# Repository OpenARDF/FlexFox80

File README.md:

# FlexFox80
A very configurable remote-controllable 80m ARDF transmitter. It has no external buttons or switches, and contains its own webserver and is configured using most WiFi-capable devices, such as smartphones, tablets, or laptops.

Flexfox can be configured to function as an 80m "fox" transmitter for any type of Amateur Radio Direction Finding event, such as classic, sprint, or even foxoring.  

Photo: Prototype FlexFox80 Assembled with 12V 6AH Battery Underneath

<b>KiCad</b>

The KiCad folder holds files for generating the schematic, BOM, and PCB files using KiCad. 

<b>Software</b>

The Software folder holds files for compiling executable code using Atmel Studio 7. 

Photo: Prototype FlexFox80 with Transparent Cover Removed

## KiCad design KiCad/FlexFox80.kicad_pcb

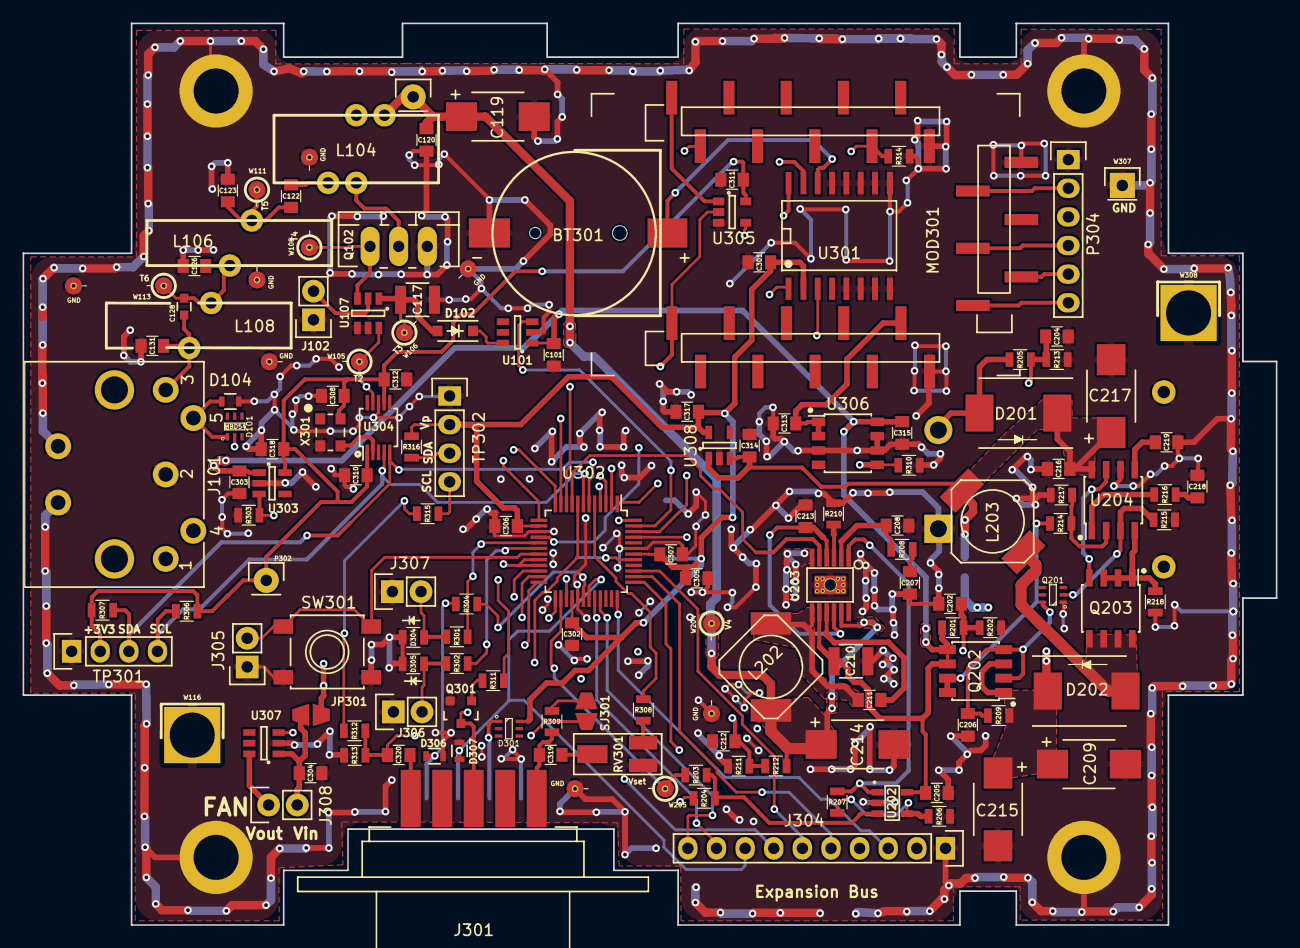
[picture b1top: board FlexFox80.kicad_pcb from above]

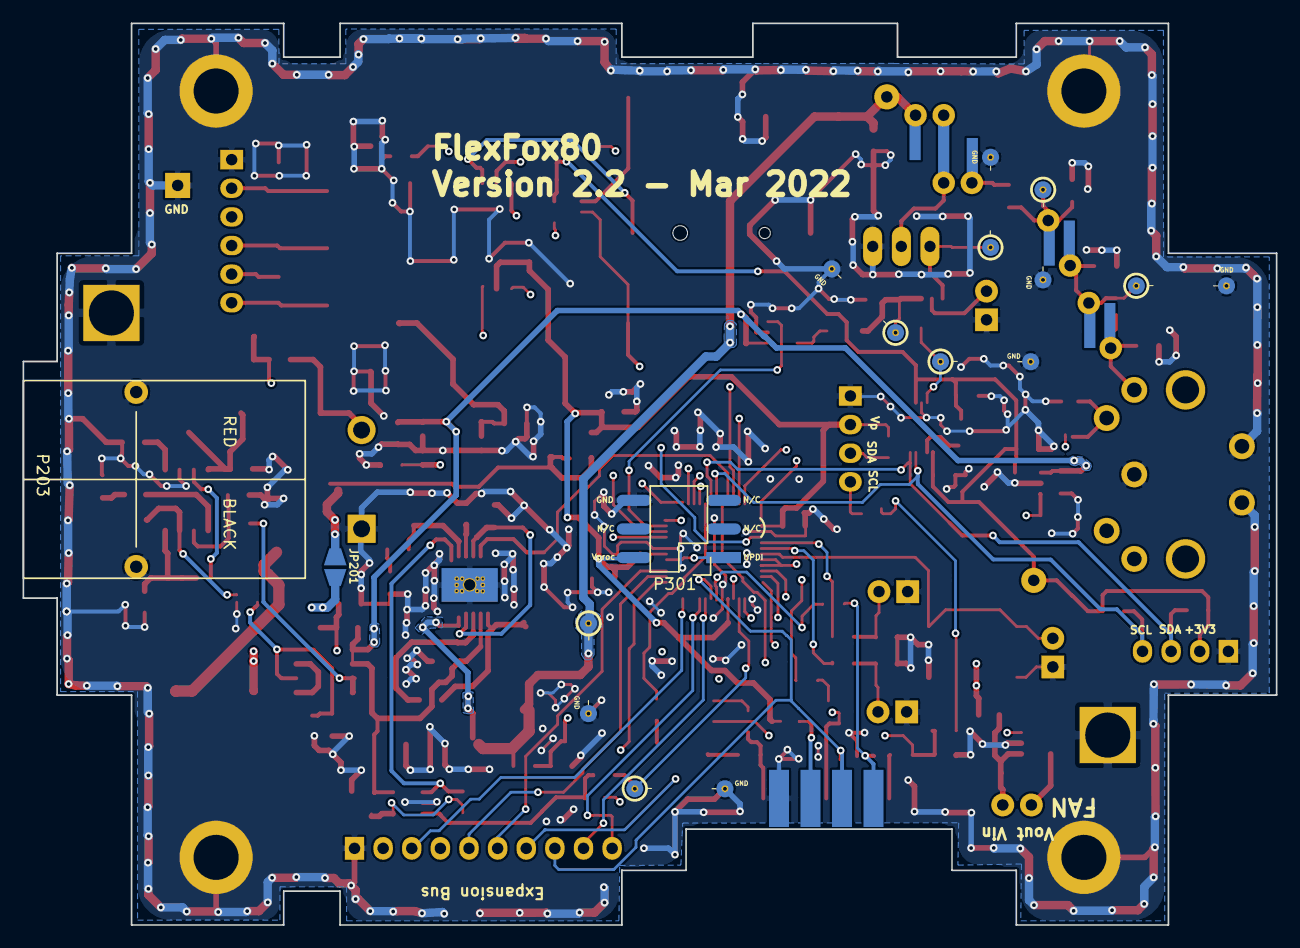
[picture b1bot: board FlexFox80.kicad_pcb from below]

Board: 4 copper layers, 111.2 x 80.0 mm, 143 parts (3 on the bottom side), 94 nets.

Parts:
BT301: CR1220; BC501SM_CR1220_BAT_Handsolder
C101, C205, C216, C304, C305: 10uF; C_0805
C117, C210: 22uF; C_1210
C119, C214, C217: 47uF low ESR; C_2917
C120, C122, C310, C312: 470nF; C_0805
C123, C131: 1100pF; C_0805
C126: 1800pF; C_0805
C128: 91pF; C_0603
C202, C204, C206, C211, C212, C302, C306, C307, C308, C311, C319, C320: 100nF; C_0805
C207: 270pF; C_0805
C208: 10pF; C_0805
C209, C215: 150uF low ESR; C_2917
C213, C219, C301: 1uF; C_0805
C218: 10nF; C_0805
C303, C313, C314, C315, C317, C318: 4.7uF; C_0805
D101, D301: MBD54; SOT-363-0.65_MBD54
D102: 4.7V; SOD-123
D104, D306, D307: ESD; R_0603
D201, D202: B530; DO-214AB
D304: GREEN; D_0805
D305: RED; D_0805
J101: DIN-5_180degree; SDF-50J
J102, J305, J306, J307, J308: Conn_01x02; Pin_Header_Straight_1x02
J203: V4; Pin_Header_Straight_1x01_circle_pad
J301: DB9_Female; DB9F_CI
J304: Conn_01x10; Pin_Header_Straight_1x10
JP201: Boost Bypass; Solder-Jumper-NO-SMD-Pad_Small
JP301: Jumper_NO_Small; Solder-Jumper-NO-SMD-Pad_Small
L104: 9T #24 Bifilar T50-43; Toroid_T-50A_TH_BF_CT_Vertical
L106, L108: 2.7uH; Toroid_T-60_2TH_Vertical
L202, L203: 6.8uH; CDR7D28MN
MOD301: HUZZAH_ESP8266_Breakout; Adafruit_HUZZAH_ESP8266_Breakout_SM
P203: Power Pole; PowerPole-ASMPP30-1x2
P301: ISP/PDI; SM_Pin_Header_Straight_2x03
P302: Thru; Pin_Header_Straight_1x01
P304: Header; Pin_Header_Straight_1x06
Q102: IRF610; TO-220_Neutral123_Vertical_LargePads
Q201: MUN5213DW1; SOT-363-0.65
Q202: DMP4025LSD; SOIC-8_3.9x4.9mm_Pitch1.27mm
Q203: RJK0354DSP; SOIC-8_3.9x4.9mm_Pitch1.27mm
Q301: PN2222A; SOT-23
R201, R205, R212: 162k; R_0805
R202: 49.9k; R_0805
R203, R206, R208: 27k; R_0805
R204: 392k; R_0805
R207, R209, R210, R308, R313: 100k; R_0805
R211, R213, R214, R215, R216, R303, R306, R307, R310, R311, R315, R316: 10k; R_0805
R217: 1.1k; R_0805
R218: 0.01 0.5W; R_0805
R301, R302: 470; R_0805
R304: 10; R_0805
R309: 2.2k; R_0805
R312, R314: 560k; R_0805
RV301: 10k Pot; Potentiometer_ST32ET_Handsolder
SJ301: SolderJumper_2_Open; Solder-Jumper-NO-SMD-Pad_Small
SW301: SPST; PTS645SL50SMTR92
TP301: I2C1; Pin_Header_Straight_1x04
TP302: I2C0; Pin_Header_Straight_1x04
U101, U307: TPS22810DBVT; SOT-23-6
U107: LM5134B; SOT-23-6-LM5134
U202: OPA171; SOT-23-5_MCP
U203: LTC3600; SSOP-12_Pad_Handsolder
U204: MIC2196; SOIC-8_3.9x4.9mm_Pitch1.27mm
U301: DS3231; SO16
U302: AVR128DA48; TQFP-48_7x7mm_Pitch0.5mm_AVR128DA48
U303, U308: LD2985BM33R; SOT-23-5
U304: SI5351A; MSOP-10_3x3mm_Pitch0.5mm
U305: 74HC1G08; SOT-23-5
U306: LT1763CS8-5; SOIC-8_3.9x4.9mm_Pitch1.27mm
W105: T2; Measurement_Point_ScopeProbe_Round-SMD-2sides-Pad_Small
W106: T3; Measurement_Point_ScopeProbe_Round-SMD-2sides-Pad_Small
W108: T4; Measurement_Point_ScopeProbe_Round-SMD-2sides-Pad_Small
W111: T5; Measurement_Point_ScopeProbe_Round-SMD-2sides-Pad_Small
W113: T6; Measurement_Point_ScopeProbe_Round-SMD-2sides-Pad_Small
W116: GND; Pin_Header_Straight_1x01
W204: V4; Measurement_Point_ScopeProbe_Round-SMD-2sides-Pad_Small
W205: Vset; Measurement_Point_ScopeProbe_Round-SMD-2sides-Pad_Small
W307, W308: CONN_01X01; Pin_Header_Straight_1x01
X301: 25.MHZ TCXO; TXETCLSANF-25.000MHZ

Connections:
3V3_PWR_ENABLE: R303.2, U302.3, U303.3
32KHZ_SQUAREWAVE: U301.1, U302.16
80M_ANTENNA_DETECT: D101.1, D104.1, J101.5, U302.20, U302.21
+2to+12V: C119.1, C120.1, C214.1, J203.1, L104.1, L202.2, R212.1, U203.11, W204.1
+3V3_L8: C308.1, C310.1, C311.2, C312.1, C318.2, J304.2, P302.1, R204.1, R306.1, R307.1, TP301.2, U303.5, U304.1, U304.7, U305.5, X301.4
+12V: C101.2, C205.2, C210.1, C303.2, C315.2, JP301.2, Q202.5, Q202.6, R201.2, U101.1, U202.5, U203.8, U303.1, U306.8
/Digital/ADC7: MOD301.13, R314.1, U302.27
/Digital/PC5: R301.2, U302.17
/Digital/PC6: R302.2, U302.18
/Digital/PC7: J305.2, SW301.1, U302.19
/Digital/PE2: J304.9, U302.32
/Digital/PE3: J304.10, U302.33
/Digital/PF2: J304.3, U302.36
/Digital/PF3: J304.4, U302.37
/Digital/PF4: J304.5, U302.38
/Digital/PF5: J304.6, U302.39
/Digital/SCL1: R306.2, TP301.4, U302.7, U304.4
/Digital/SDA1: R307.2, TP301.3, U302.6, U304.5
/Digital/TXD4: J304.7, R304.1, U302.30
CLK1: U107.6, U304.9, W105.1
DAC_OUTPUT: R203.2, U302.26, W205.1
EXTERNAL_3.6V-15V_SUPPLY: C216.2, C217.1, C314.2, D201.1, JP201.2, L203.2, U204.8, U308.1, U308.3
FAN_ENABLE: U302.45, U307.3
FET_DRIVER_ENABLE: U101.3, U302.47
GND: BT301.2, C101.1, C117.2, C119.2, C120.2, C123.2, C126.1, C131.2, C202.2, C204.1, C205.1, C206.2, C207.2, C208.2, C209.2, C210.2, C212.1, C213.2, C214.2, C215.2, C216.1, C217.2, C218.2, C219.2, C301.2, C302.1, C303.1, C304.2, C305.1, C306.1, C307.1, C308.2, C310.2, C311.1, C312.2, C313.1, C314.1, C315.1, C317.1, C318.1, D104.2, D304.1, D305.1, D306.2, D307.2, J101.2, J101.E, J102.1, J301.6, J304.1, J305.1, J306.1, J307.1, MOD301.10, MOD301.11, MOD301.21, P203.1, P203.E, P301.6, P304.1, Q102.3, Q201.1, Q301.2, R202.2, R206.2, R210.2, R211.2, R213.2, R215.1, R217.1, R218.1, R303.1, R310.2, R313.2, R314.2, RV301.3, SW301.2, TP301.1, TP302.1, U101.2, U107.4, U107.5, U202.2, U203.6, U203.13, U204.6, U301.5, U301.6, U301.7, U301.8, U301.9, U301.10, U301.11, U301.12, U301.13, U302.15, U302.29, U302.43, U303.2, U304.8, U305.3, U306.3, U306.6, U306.7, U307.2, U308.2, W105.2, W106.2, W108.2, W111.2, W113.2, W116.1, W204.2, W205.2, W307.1, W308.1, X301.2
MAIN_PWR_ENABLE: Q201.2, R215.2, U204.3, U302.8
unnamed: BT301.1, U301.14
unnamed: C117.1, D102.2, U107.1, W106.1
unnamed: C122.1, L104.3
unnamed: C122.2, C123.1, L106.1, W111.1
unnamed: C126.2, C128.2, L106.2, L108.1, W113.1
unnamed: C128.1, C131.1, J101.3, L108.2
unnamed: C206.1, Q201.6, Q202.2, Q202.4, R209.1
unnamed: C207.1, R208.2
unnamed: C208.1, R208.1, U203.2
unnamed: C209.1, C215.1, D202.1, JP201.1, Q202.1, Q202.3, R209.2
unnamed: C211.1, L202.1, U203.7
unnamed: C211.2, U203.9
unnamed: C213.1, U203.4, U203.10
unnamed: C218.1, R216.1
unnamed: C219.1, U204.5
unnamed: C304.1, J308.2, JP301.1, U307.1
unnamed: C313.2, MOD301.9, U306.1, U306.2
unnamed: C319.1, RV301.2
unnamed: C319.2, J301.1, R309.2
unnamed: C320.2, J301.5
unnamed: D102.1, U101.6
unnamed: D201.2, P203.2, R205.1
unnamed: D202.2, L203.1, Q203.5, Q203.6, Q203.7, Q203.8
unnamed: D301.1, J301.7
unnamed: D304.2, J307.2, R301.1
unnamed: D305.2, J306.2, R302.1
unnamed: J102.2, U107.2
unnamed: J301.3, Q301.3, SJ301.2
unnamed: J308.1, U307.6
unnamed: L104.2, Q102.2
unnamed: MOD301.20, U305.1
unnamed: MOD301.22, P304.2
unnamed: MOD301.24, P304.4
unnamed: MOD301.25, P304.5
unnamed: MOD301.26, P304.6
unnamed: P301.1, U302.41
unnamed: Q102.1, U107.3, W108.1
unnamed: Q202.7, Q202.8, R214.2
unnamed: Q203.1, Q203.2, Q203.3, R218.2, U204.4
unnamed: Q203.4, U204.7
unnamed: Q301.1, R311.1
unnamed: R203.1, R204.2, U202.3
unnamed: R206.1, R207.2, U202.4
unnamed: R207.1, U202.1, U203.1
unnamed: R210.1, U203.3
unnamed: R214.1, R217.2, U204.2
unnamed: R216.2, U204.1
unnamed: R308.2, RV301.1
unnamed: R309.1, SJ301.1
unnamed: U304.2, X301.3
PROC_HT_AUDIO_IN: C320.1, R312.2, R313.1, U302.22
PROC_PTT_OUT: R311.2, U302.4
PROC_TONE_OUT: R308.1, U302.5
RTC_SCL: R315.2, TP302.4, U301.16, U302.13
RTC_SDA: R316.2, TP302.3, U301.15, U302.12
RTC_SQW: U301.3, U302.46
RXD_TO_FTDI: D307.1, J301.8, J304.8, U302.31
TXD_TO_FTDI: D306.1, J301.9, R304.2
TX_+12_VOLTAGE: C202.1, R201.1, R202.1, U302.24
TX_BATTERY_VOLTAGE: C204.2, R205.2, R213.1, U302.23
TX_FINAL_VOLTAGE_ENABLE: U203.5, U302.9
TX_PA_VOLTAGE: C212.2, R211.1, R212.2, U302.25
Vproc: C301.1, C302.2, C305.2, C306.2, C307.2, C317.2, D301.6, P301.2, R312.1, R315.1, R316.1, TP302.2, U301.2, U302.14, U302.28, U302.42, U308.5
WIFI_ENABLE: R310.1, U302.1, U306.5
WIFI_RX: MOD301.19, U302.10
WIFI_TX: U302.11, U305.4
~ANT_CONNECT_INT: D101.2, U302.48
~WIFI_RESET: MOD301.1, U302.2, U305.2

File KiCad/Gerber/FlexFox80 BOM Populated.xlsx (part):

FlexFox80
Ref | Value | QTY PER | Footprint | Description | Digi-Key Part No. | LCSC Part No. | Link | Manufacturer | Manufacturer PN | Comments
C123 C131 | 1100pF | 2 | Capacitors_SMD:C_0805 | CAP CER 1100PF 50V NP0 0805 | 399-14552-1-ND | C2327793 | <a href="https://www.digikey.com/products/en?keywords=399-14552-1-ND">Link</a> | KEMET | C0805C112J5GAC7800
C120 C122 C310 C312 | 470nF | 4 | Capacitors_SMD:C_0805 | CAP CER 0.47UF 100V X7R 0805 | 478-9924-1-ND | C342818 | <a href="https://www.digikey.com/products/en?keywords=478-9924-1-ND">Link</a> | AVX Corporation | 08051C474K4Z2A
C126 | 1800pF | 1 | Capacitors_SMD:C_0805 | CAP CER 1800PF 100V C0G 0805 | 445-5752-1-ND | C2173329 | <a href="https://www.digikey.com/products/en?keywords=445-5752-1-ND">Link</a> | TDK Corporation | CGA4F2C0G2A182J085AA
C128 | 91pF | 1 | Capacitors_SMD:C_0603 | CAP CER 91PF 100V NP0 0603 | 478-10247-1-ND | C2170042 | <a href="https://www.digikey.com/products/en?keywords=478-10247-1-ND">Link</a> | KYOCERA AVX | 06031U910FAT2A
C119 C214 C217 | 47uF low ESR | 3 | Capacitors_SMD:C_2917 | CAP TANT 47UF 10% 20V 2917 | 399-3904-1-ND | C122333 | <a href="https://www.digikey.com/products/en?keywords=399-3904-1-ND">Link</a> | KEMET | T495X476K020ATE150
C117 C210 | 22uF | 2 | Capacitors_SMD:C_1210 | CAP CER 22UF 25V X5R 1210 | 1276-3373-1-ND | C337455 | <a href="https://www.digikey.com/products/en?keywords=1276-3373-1-ND">Link</a> | Samsung Electro-Mechanics | CL32A226MAJNNNE
C101 C205 C216 C305 C304 | 10uF | 5 | Capacitors_SMD:C_0805 | CAP CER 10UF 25V X5R 0805 | 490-5523-1-ND | C84416 | <a href="https://www.digikey.com/products/en?keywords=490-5523-1-ND">Link</a> | Murata Electronics | GRM21BR61E106KA73L
C213 C219 C301 | 1uF | 3 | Capacitors_SMD:C_0805 | CAP CER 1UF 16V X7R 0805 | 311-1365-1-ND | C344171 | <a href="https://www.digikey.com/products/en?keywords=311-1365-1-ND">Link</a> | Yageo | CC0805KKX7R7BB105
C207 | 270pF | 1 | Capacitors_SMD:C_0805 | CAP CER 270PF 50V C0G/NP0 0805 | 1276-2624-1-ND | C161109 | <a href="https://www.digikey.com/products/en?keywords=1276-2624-1-ND">Link</a> | Samsung Electro-Mechanics | CL21C271GBANNNC
C208 | 10pF | 1 | Capacitors_SMD:C_0805 | CAP CER 10PF 200V C0G/NP0 0805 | 478-10457-1-ND | C344177 | <a href="https://www.digikey.com/products/en?keywords=478-10457-1-ND">Link<a/> | AVX Corporation | 08052U100FAT2A
C206 C211 C202 C204 C212 C306 C307 C302 C319 C320 C311 C308 | 100nF | 12 | Capacitors_SMD:C_0805 | CAP CER 0.1UF 50V X7R 0805 | 478-1395-1-ND | C360619 | <a href="https://www.digikey.com/products/en?keywords=478-1395-1-ND">Link</a> | AVX Corporation | 08055C104KAT2A
C215 C209 | 150uF low ESR | 2 | Capacitors_SMD:C_2917 | CAP TANT 150UF 10% 20V 2917 | 478-5253-1-ND | C444765 | <a href="https://www.digikey.com/products/en?keywords=478-5253-1-ND">Link</a> | AVX Corporation | TPME157K020R0035
C218 | 10nF | 1 | Capacitors_SMD:C_0805 | CAP CER 10000PF 50V NP0 0805 | 478-10068-1-ND | C527201 | <a href="https://www.digikey.com/products/en?keywords=478-10068-1-ND">Link</a> | AVX Corporation | 08055A103JAT2A
C303 C318 C317 C314 C313 C315 | 4.7uF | 6 | Capacitors_SMD:C_0805 | CAP CER 4.7UF 25V X7R 0805 | 587-2990-1-ND | C162420 | <a href="https://www.digikey.com/products/en?keywords=587-2990-1-ND">Link</a> | Taiyo Yuden | TMK212AB7475KG-T
D104 D306 D307 | ESD | 3 | Resistors_SMD:R_0603 | VARISTOR 0603 | CG0603MLC-05LECT-ND | C2655331 | <a href="https://www.digikey.com/products/en?keywords=CG0603MLC-05LECT-ND">Link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 | Bourns Inc. | CG0603MLC-05LE
D101 D301 | MBD54 | 2 | TO_SOT_Packages_SMD:SOT-363-0.65 | DIODE ARRAY SCHOTTKY 30V SC88 | MBD54DWT1GOSCT-ND | C152486 | <a href="https://www.digikey.com/products/en?keywords=MBD54DWT1GOSCT-ND">Link</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 | ON Semiconductor | MBD54DWT1G
D102 | 4.7V | 1 | Diodes_SMD:SOD-123_Handsolder | DIODE ZENER 4.7V 500MW SOD123 | BZT52C4V7-13FDICT-ND | C151054 | <a href="https://www.digikey.com/products/en?keywords=BZT52C4V7-13FDICT-ND">Lin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 | Diodes Incorporated | BZT52C4V7-13-F
D202 D201 | B530 | 2 | Diodes_SMD:DO-214AB | DIODE SCHOTTKY 30V 5A SMC | B530C-FDICT-ND | C110488 | <a href="https://www.digikey.com/products/en?keywords=B530C-FDICT-ND">Link</a> | Diodes Incorporated | B530C-13-F
D305 | RED | 1 | Resistors_SMD:R_0805 | LED RED CLEAR 0805 SMD | 732-4984-1-ND | C72037 | <a href="https://www.digikey.com/products/en?keywords=732-4984-1-ND ">Link</a> | Wurth Elektronik | 150080RS75000
D304 | GREEN | 1 | Resistors_SMD:R_0805 | LED GREEN CLEAR 0805 SMD | 732-4983-1-ND | C98224 | <a href="https://www.digikey.com/products/en?keywords=732-4983-1-ND">Link</a> | Wurth Elektronik | 150080GS75000
L202 L203 | 6.8uH | 2 | Inductors:CDR7D28MN | FIXED IND 6.8UH 2.75A 46.3 MOHM | 308-1328-1-ND |  | <a href="https://www.digikey.com/products/en?keywords=308-1328-1-ND">Link</a> | Sumida America Components Inc. | CDR7D28MNNP-6R8NC
Q201 | MUN5213DW1 | 1 | TO_SOT_Packages_SMD:SOT-363-0.65 | TRANS PREBIAS 2NPN 50V SC88 | MUN5213DW1T1GOSCT-ND | C95381 | <a href="https://www.digikey.com/products/en?keywords=MUN5213DW1T1GOSCT-ND">Lin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 | ON Semiconductor | MUN5213DW1T1G
Q202 | DMP4025LSD | 1 | Housings_SOIC:SOIC-8_3.9x4.9mm_Pitch1.27mm | MOSFET 2P-CH 40V 6.9A 8SO | DMP4025LSD-13DICT-ND | C150763 | <a href="https://www.digikey.com/products/en?keywords=DMP4025LSD-13DICT-ND">Lin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 | Diodes Incorporated | DMP4025LSD-13
Q203 | RJK0354DSP | 1 | Housings_SOIC:SOIC-8_3.9x4.9mm_Pitch1.27mm | MOSFET N-CH 30V 16A 8SOP | RJK0354DSP-00#J0CT-ND | C919563 | <a href="https://www.digikey.com/products/en?keywords=RJK0354DSP-00#J0CT-ND">Li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 | Renesas Electronics America Inc | RJK0354DSP-00#J0
Q301 | PN2222A | 1 | TO_SOT_Packages_SMD:SOT-23 | TRANS NPN 40V 0.6A SOT23 | MMBT2222ATPMSCT-ND | C194252 | <a href="https://www.digikey.com/products/en?keywords=MMBT2222ATPMSCT-ND">Link<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 | Micro Commercial Co | MMBT2222A-TP
R204 | 392k | 1 | Resistors_SMD:R_0805 | RES SMD 392K OHM 1% 1/8W 0805 | 311-392KCRCT-ND | C273847 | <a href="https://www.digikey.com/products/en?keywords=311-392KCRCT-ND">Link</a> | Yageo | RC0805FR-07392KL
R207 R209 R210 R313 R308 | 100k | 5 | Resistors_SMD:R_0805 | RES SMD 100K OHM 1% 1/8W 0805 | 311-100KCRCT-ND | C103905 | <a href="https://www.digikey.com/products/en?keywords=311-100KCRCT-ND">Link</a> | Yageo | RC0805FR-07100KL
R212 R205 R201 | 162k | 3 | Resistors_SMD:R_0805 | RES SMD 162K OHM 1% 1/8W 0805 | 311-162KCRCT-ND | C416820 | <a href="https://www.digikey.com/products/en?keywords=311-162KCRCT-ND">Link</a> | Yageo | RC0805FR-07162KL
R203 R208 R206 | 27k | 3 | Resistors_SMD:R_0805 | RES SMD 27K OHM 1% 1/8W 0805 | 311-27.0KCRCT-ND | C139896 | <a href="https://www.digikey.com/products/en?keywords=311-27.0KCRCT-ND">Link</a> | Yageo | RC0805FR-0727KL
R213 R214 R211 R216 R215 R306 R307 R310 R311 R303 R315 R316 | 10k | 12 | Resistors_SMD:R_0805 | RES SMD 10K OHM 1% 1/8W 0805 | 311-10KLGCT-ND | C38522 | <a href="https://www.digikey.com/products/en?keywords=311-10KLGCT-ND">Link</a> | Yageo | AC0805FR-0710KL
R217 | 1.1k | 1 | Resistors_SMD:R_0805 | RES SMD 1.1K OHM 1% 1/8W 0805 | 311-1.10KCRCT-ND | C352257 | <a href="https://www.digikey.com/products/en?keywords=311-1.10KCRCT-ND">Link</a> | Yageo | RC0805FR-071K1L
R218 | 0.01 0.5W | 1 | Resistors_SMD:R_0805 | RES 0.01 OHM 1% 1/2W 0805 | 408-1544-1-ND | C728271 | <a href="https://www.digikey.com/products/en?keywords=408-1544-1-ND">Link</a> | Susumu | KRL1220E-M-R010-F-T5
R202 | 49.9k | 1 | Resistors_SMD:R_0805 | RES SMD 49.9K OHM 0.1% 1/8W 0805 | YAG4990CT-ND | C218598 | <a href="https://www.digikey.com/products/en?keywords=YAG4990CT-ND">Link</a> | Yageo | RT0805BRE0749K9L
R304 | 10 | 1 | Resistors_SMD:R_0805 | RES SMD 10 OHM 1% 1/8W 0805 | 311-10.0CRCT-ND | C96347 | <a href="https://www.digikey.com/products/en?keywords=311-10.0CRCT-ND">Link</a> | Yageo | RC0805FR-0710RL
R312 R314 | 560k | 2 | Resistors_SMD:R_0805 | RES SMD 560K OHM 1% 1/8W 0805 | 13-RT0805FRE07560KLCT-ND | C352198 | <a href="https://www.digikey.com/products/en?keywords=13-RT0805FRE075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"… | Yageo | RT0805FRE07560KL
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
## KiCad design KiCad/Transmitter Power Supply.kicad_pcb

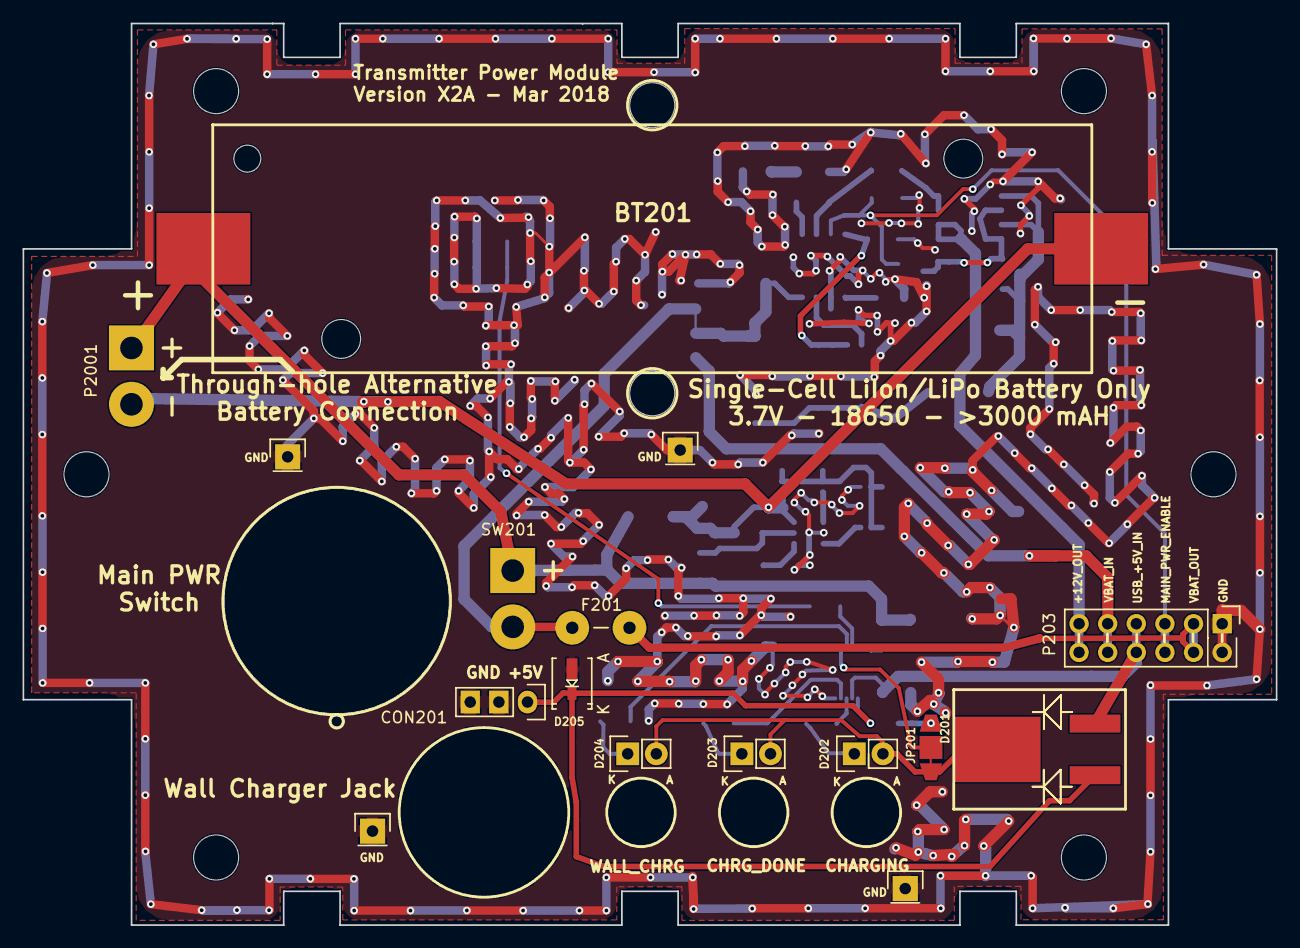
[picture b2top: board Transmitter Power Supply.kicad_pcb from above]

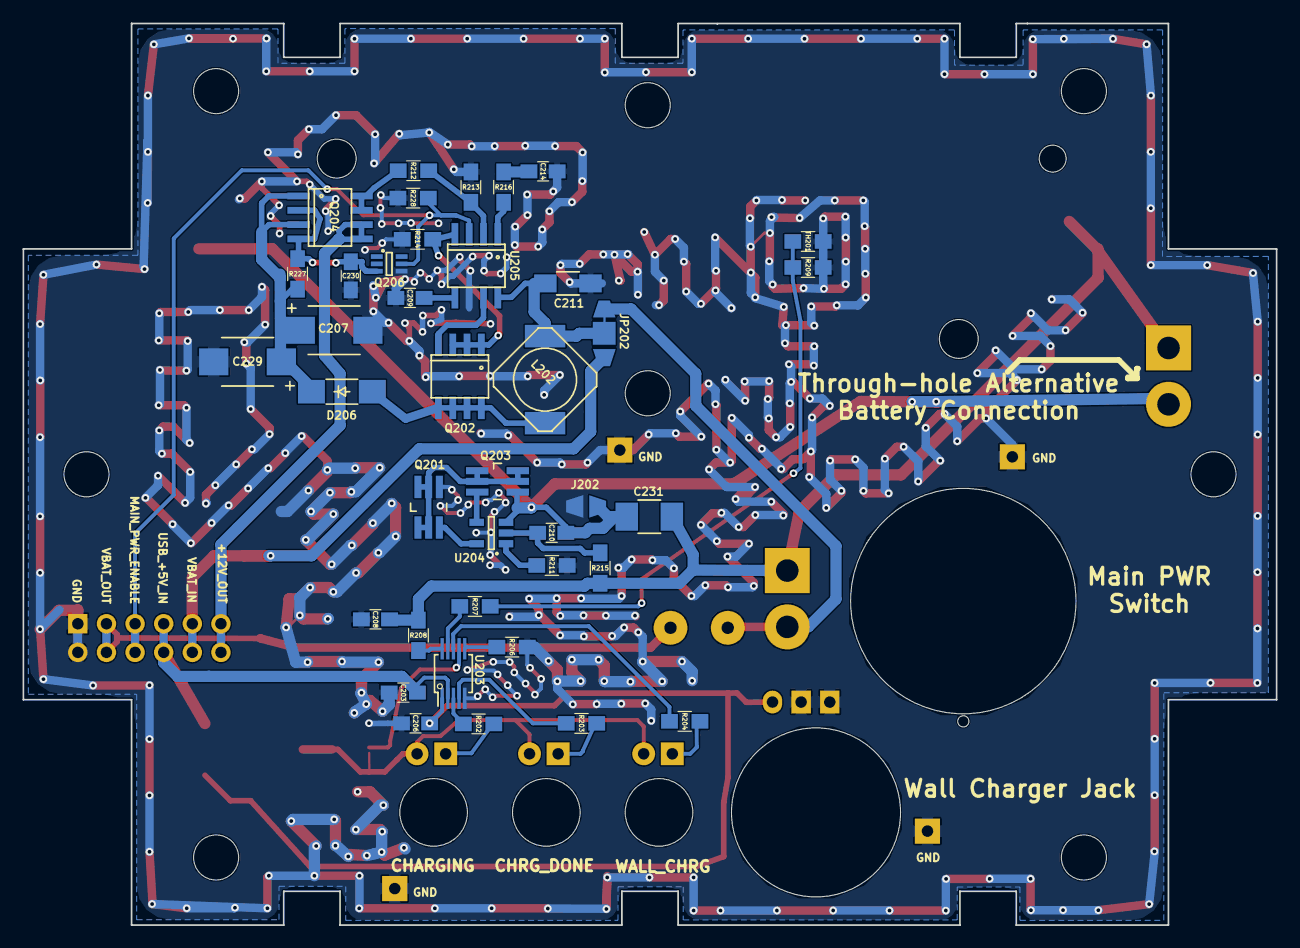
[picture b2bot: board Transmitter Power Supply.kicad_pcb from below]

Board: 2 copper layers, 111.2 x 80.0 mm, 63 parts (39 on the bottom side), 38 nets.

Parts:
4mm thru, 4mm thru#2: MountingHole_4mm; MountingHole_4mm_Outlined
4mm thru#3, 4mm thru#4, 4mm thru#5, 4mm thru#6, 4mm thru#7, 4mm thru#8: MountingHole_4mm
BT201: 1-Cell LiPo/Li-Ion; 1042P_18650_BAT_Handsolder
C203, C206, C208, C209: 10uF; C_0805_HandSoldering
C207, C229: 150 uF low esr; C_2917_7343_Metric_HandSoldering
C210, C230: 100nF; C_0805_HandSoldering
C211: 47uF; C_1206_HandSoldering
C214: 10nF; C_0805_HandSoldering
C231: 100uF; C_1210_HandSoldering
CON201: EJ508A; Pin_Header_Straight_1x03
D201: Dual_Schottky_Common_Cathode_DPAK369; DPAK_369C_DUAL_DIODE_Handsolder
D202: RED; Pin_Header_Straight_1x02
D203: GREEN; Pin_Header_Straight_1x02
D204: ORANGE; Pin_Header_Straight_1x02
D205: 5V Zener; MicroSMP_Handsoldering
D206: B530; CMS04_Handsolder
F201: 1A Therm Fuse; Resistor_Horizontal_RM5mm
J202: Jumper_NO_Small; Solder-Jumper-NO-SMD-Pad_Small
J1001, J1001#2, J1001#3: CONN_01X01; Pin_Header_Straight_1x01
J1002: P0; Pin_Header_Straight_1x01
JP201, JP202: JUMPERx3_1-2_NC; Solder-Jumperx3-NC_1-2_SMD-Pad_Small
L202: 6.8uH; CDR7D28MN
P203: To Transmitter Board; Pin_Header_Straight_2x06
P2001: CONN_01X02; PolarizedConnection_2.00mmDrill
Q201, Q203: AO6404; TSOT-6-MK06A_Handsoldering
Q202: SI4884BDY; SO-8_Handsolder
Q204: DMP4025LSD; SO-8_Handsolder
Q206: MUN5211DW1T1G; SOT-363_Handsolder
R202, R203, R204, R206: 1k; R_0805_HandSoldering
R207, R208: 0; R_0805_HandSoldering
R209: NP; R_0805_HandSoldering
R211: 2.7k; R_0805_HandSoldering
R212, R216, R228: 10k; R_0805_HandSoldering
R213: 1.1k; R_0805_HandSoldering
R214: 0.01 0.5W; R_0805_HandSoldering
R215: 470; R_0805_HandSoldering
R227: 100k; R_0805_HandSoldering
SW201: Main Pwr; PolarizedConnection_2.00mmDrill
TH201: Vishay NTCS0805E3103FLT; R_0805_HandSoldering
U203: MCP73837; MSOP-10_3x3mm_Pitch0.5mm_Handsolder
U204: AP9101CK; SOT-25_Handsolder
U205: MIC2196; SO-8_Handsolder

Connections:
BOOST_ENABLE: P203.5, P203.6, Q206.5, R228.2, U205.3
GNDA_L8: C203.2, C206.1, C207.2, C208.2, C209.2, C211.2, C214.1, C229.2, C230.1, CON201.2, CON201.3, D205.2, J202.2, J1001.1, J1001#2.1, J1001#3.1, J1002.1, JP201.3, P203.1, P203.2, Q201.4, Q206.4, R206.1, R209.1, R211.1, R213.1, R214.1, R228.1, TH201.2, U203.5, U205.6
LiIon_PWR: F201.1, JP202.1, SW201.2
unnamed: BT201.1, C208.1, C231.1, P2001.1, R208.1, R215.2, SW201.1
unnamed: BT201.2, C210.2, C231.2, J202.1, P2001.2, Q203.4, U204.3
unnamed: C206.2, CON201.1, D201.1, D205.1, U203.1
unnamed: C207.1, C229.1, D206.1, Q204.1, Q204.3, R227.1
unnamed: C209.1, U205.5
unnamed: C210.1, R215.1, U204.2
unnamed: C211.1, JP202.2, L202.1, U205.8
unnamed: C214.2, R216.2
unnamed: C230.2, Q204.2, Q204.4, Q206.3, R227.2
unnamed: D201.4, D202.2, D203.2, D204.2, JP201.1
unnamed: D202.1, R202.2
unnamed: D203.1, R203.2
unnamed: D204.1, R204.2
unnamed: D206.2, L202.2, Q202.5, Q202.6, Q202.7, Q202.8
unnamed: F201.2, P203.3, P203.4
unnamed: JP201.2, U203.7
unnamed: JP202.3, P203.9, P203.10
unnamed: P203.11, P203.12, Q204.5, Q204.6
unnamed: Q201.1, Q201.2, Q201.5, Q201.6, Q203.1, Q203.2, Q203.5, Q203.6
unnamed: Q201.3, U204.5
unnamed: Q202.1, Q202.2, Q202.3, R214.2, U205.4
unnamed: Q202.4, U205.7
unnamed: Q203.3, U204.4
unnamed: Q204.7, Q204.8, R212.2
unnamed: R202.1, U203.3
unnamed: R203.1, U203.4
unnamed: R204.1, U203.8
unnamed: R206.2, U203.6
unnamed: R207.1, R209.2, TH201.1
unnamed: R207.2, U203.9
unnamed: R208.2, U203.10
unnamed: R211.2, U204.1
unnamed: R212.1, R213.2, U205.2
unnamed: R216.1, U205.1
USB_+5V_in: C203.1, D201.3, P203.7, P203.8, U203.2

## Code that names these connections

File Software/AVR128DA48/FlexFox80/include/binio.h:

/*
 *  MIT License
 *
 *  Copyright (c) 2022-2026 DigitalConfections
 *
 *  Permission is hereby granted, free of charge, to any person obtaining a copy
 *  of this software and associated documentation files (the "Software"), to deal
 *  in the Software without restriction, including without limitation the rights
 *  to use, copy, modify, merge, publish, distribute, sublicense, and/or sell
 *  copies of the Software, and to permit persons to whom the Software is
 *  furnished to do so, subject to the following conditions:
 *
 *  The above copyright notice and this permission notice shall be included in all
 *  copies or substantial portions of the Software.
 *
 *  THE SOFTWARE IS PROVIDED "AS IS", WITHOUT WARRANTY OF ANY KIND, EXPRESS OR
 *  IMPLIED, INCLUDING BUT NOT LIMITED TO THE WARRANTIES OF MERCHANTABILITY,
 *  FITNESS FOR A PARTICULAR PURPOSE AND NONINFRINGEMENT. IN NO EVENT SHALL THE
 *  AUTHORS OR COPYRIGHT HOLDERS BE LIABLE FOR ANY CLAIM, DAMAGES OR OTHER
 *  LIABILITY, WHETHER IN AN ACTION OF CONTRACT, TORT OR OTHERWISE, ARISING FROM,
 *  OUT OF OR IN CONNECTION WITH THE SOFTWARE OR THE USE OR OTHER DEALINGS IN THE
 *  SOFTWARE.
 */

/*
 * AVR digital input and output helpers.
 */

#ifndef __BINIO_H__
#define __BINIO_H__

#include "defs.h"

/* PORTA *************************************************************************************/
#define V3V3_PWR_ENABLE 7
#define WIFI_RESET 6
#define WIFI_ENABLE 5
#define ANT_CONNECT_INT 4
#define FET_DRIVER_ENABLE 3
#define RTC_SQW 2
#define FAN_ENABLE 1
// #define unused 0

/* PORTB *************************************************************************************/
#define TX_FINAL_VOLTAGE_ENABLE 5
#define MAIN_PWR_ENABLE 4
#define SCL1 3
#define SDA1 2
#define PROC_TONE_OUT 1
#define PROC_PTT_OUT 0

/* PORTC *************************************************************************************/
#define SWITCH 7
#define LED_RED 6
#define LED_GREEN 5
// #define unused 0
#define RTC_SCL 3
#define RTC_SDA 2
#define FRoM_WIFI_TX 1
#define TO_WIFI_RX 0

/* PORTD *************************************************************************************/
#define WIFI_MODULE_DETECT 7
#define DAC_OUTPUT 6
#define TX_PA_VOLTAGE 5
#define TX_12_VOLTAGE 4
#define TX_BATTERY_VOLTAGE 3
#define PROC_HT_AUDIO_IN 2
#define X80M_ANTENNA_DETECT 1
#define X80M_ANTENNA_DETECT_V 0

/* PORTE *************************************************************************************/
// TBD

/* PORTF *************************************************************************************/
#define X32KHZ_SQUAREWAVE 0


void BINIO_init(void);
void BINIO_sleep(void);
void debounce(void);
uint8_t portCdebouncedVals(void);
uint8_t portDdebouncedVals(void);

class binio
{
//variables
public:
protected:
private:

//functions
public:
	binio();
	~binio();
protected:
private:
	binio( const binio &c );
	binio& operator=( const binio &c );

}; //binio

#endif //__BINIO_H__

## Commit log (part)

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2021-04-07 Baseline KiCad Files
    First KiCad files upload with no changes. Start is from 2-Band ARDF Mini Transmitter project.
2021-04-07 Changes for FlexFox80
    Wholesale changes for new project.
2021-04-07 Schematic
    Schematic changes for FlexFox80
2021-04-08 Schematic Updates
    More schematic changes
2021-04-08 Schematic changes
    Schematic
2021-04-08 Schematic
    Schematic changes
2021-04-27 Updates to Schematic
    Updates to Schematic
2021-05-10 Design Updates
    Specifying components
2021-05-10 Design Updates
    Defining parts and footprints
2021-05-11 Design Updates
    Updating schematic parts
2021-05-11 Design Updates
    Updated schematics parts descriptions
2021-05-12 PCB Updates
    o Started PCB layout
2021-05-12 PCB Updates
    Layout work
2021-05-13 PCB Layout
    Complete first pass at PCB parts layout. No traces.
2021-05-13 PCB Updates
    Work in progress - routing
2021-05-14 PCB Development
    Added more traces
2021-05-14 PCB Updates
    First cut at routing complete. DRC passes. Need to add connection to pilot pin.
2021-05-15 PCB Updates
    PCB is now ready for review. Still needs some silkscreen text added.
2021-05-16 BOM Updates
    Corrections to part information in schematic and BOMs
2021-11-06 Adding Software Files
    Project uses Microchip Studio 7 for software development
2021-11-06 Adding build files
    Build files added
2021-11-16 AVR128DA48
    Transition to new processor software development
2021-11-16 USART1 ISR
    o First implementation of ISRs for USART send and receive.
2021-11-16 Minor Bug Fix
    Removed unnecessary ISR code
2021-11-16 DEV
    DEV
2021-11-21 Development
    Development
2021-11-21 Fix
    Clear TB0 interrupt flag in ISR
2021-11-21 Development
    Set DAC statically
2021-11-22 ADC
    ADC
2021-11-22 Remove Goertzel
    Remove Goertzel
2021-11-22 Conversion to CPP
    Converted tools and project files for C++
2021-11-22 Development
    Basic ADC and Goertzel funtions added
2021-11-24 Development
    BINIO settings and interrupts
2021-11-25 Development
    Added support for two USARTS
2021-11-25 Development
    Support for swapping USART0/1 functionality
2021-11-28 Development
    EEPROM support
2021-12-01 Development
    I2C debugging
    EEPROM updates
2021-12-02 Development
    EEPROM updating
    SI5351 I2C error reporting
2021-12-03 Development
    Added conversion from epoch to string date
2021-12-03 Development
    boolean cleanup
2021-12-04 Development
    Debug of string printing
2021-12-04 AVR128DA48 Redesign
    Kicad updates for new FlexFox design
2021-12-05 Development
    I2C debugging for DS3231
2021-12-05 Development
    Add fox setting descriptive text
2021-12-08 Development
    Changes to get SYN 1 partially working
2022-01-07 Development
    Continued integration of Arducon functionality into FlexFox
2022-01-29 Updates for AVR128DA48
    o Board changes
    o Gerbers updated
2022-02-06 Updates
    o Added fan control
    o Fixed pinout for load switch device
    o Updated gerbers
    o Updated BOM
2022-02-06 Fan Control Update
    o Corrected an error in the fan control circuit
    o Updated all gerbers and fab files
2022-02-07 Updated BOM
    Updated BOM files
2022-02-07 Removed old BOM files
    o Removed some old BOM files from the folder
2022-02-17 Updated PCB
    o Changed U302 footprint to more closely match 48-TQFP (7x7) shown in the AVR128DA48 datasheet
2022-02-17 Schematic Update
    Updated footprint specified for AVR128DA48
2022-02-17 Gerber Update
    Removed flood fills of U302 ground pins.
2022-02-24 Updates
    o BOM updates
    o Gerber updates
2022-02-27 Gerber Update
    o Added J201 to optionally bypass U204
2022-02-27 Gerber Updates
    o Changed parts for C128, L203 and L204 to help with parts shortages
    o Updated footprints
    o Updated schematic
    o Updated BOM
2022-02-27 Updated Gerbers
    Corrected version date on PCB
2022-03-02 Gerber Update
    o Corrected dimensions of U203
2022-03-04 Footprint Updates
    Tweaks to PCB footprints.
    Removed solder paste from unpopulated components
2022-03-09 PCB Updates
    Adjusted clearances on PCB. All Gerbers have been updated.
2022-03-10 PCB Update
    Corrected some pad spacing issues.
2022-03-10 Update FlexFox80.kicad_pcb-bak
2022-03-10 Updated Silkscreen
    o Incremented PCB version number
2022-03-31 Latest Gerbers
    Gerbers with minor updates to silkscreen and D101, D301 footprints
2022-04-22 KiCad V6 Updates
    Mostly schematic updates for KiCad V6
2022-04-25 Readme Updates
    Added photos to Docs folder
2022-04-25 Photo Update
    Corrected photo name
2022-05-05 Software Updates
    o Numerous changes during board bring-up
2022-05-07 Reorganization
    o Added folders
    o Added Arduino sketch software for Huzzah ESP8266 support
2022-05-07 Last ATMEGA Updates
    o Replaced Software files with latest from the "Receiver Development Platform" code supporting the ATMEGA328P hardware design.
2022-05-08 HUZZAH Fixes
    o Fix for battery voltage reporting
    o Fix for WiFi sync delays caused by legacy commands for band and modulation format
2022-05-10 Development
    o Numerous changes to implement basic functionality
2022-05-11 Development
    Numerous changes to implement basic functions
2022-05-19 KiCad Updates
    o Fixes for problems found during first board build
2022-05-19 Software Development
    o Numerous bug fixes and function implementation changes.
2022-05-21 Development
    o Implemented tx inhibit when the antenna is removed
2022-05-26 Development
    o Fixed syntax error
2022-05-27 WiFi Dev
2022-05-27 Update to .gitignore
    Ignore .zip files
2022-05-27 Development
    o Minor fixes
2022-05-27 Development
    o Adding key down manual support
2022-05-29 Development
    Debugging
    Added manual.html to support use as a qrp cw transmitter
2022-05-29 Development
    o Dubugging
    o Added support for regular cw qrp radio
2022-05-31 Development
    o Implemented sending single characters and strings sent over the linkbus.
2022-05-31 Development
    Implemented html file to support simple QRP CW transmitter operation
2022-05-31 Development
    o Debug of Radio functionality
2022-05-31 Development
    Fixes to the radio interface functionality
2022-06-03 Development
    o Radio operation debugging
2022-06-03 Development
    o Bug fixes for Radio operation
2022-06-04 Development
    o Wifi debugging
    o Radio performance
2022-06-04 Development
    Fix for antenna disconnect behavior
2022-06-08 Development
    o Sleep fixes
2022-06-08 Development
    o Fixes to web socket shutdown behavior
2022-06-08 Development
    Cleanup
2022-06-09 Development
    o tweaks to start-up behavior and hardware failure detection
2022-06-09 Development
    o Cleanup of startup initialization
2022-06-13 Development
    o Minor bug fixes
    o Improvements to radio.html
    o Huzzah version bumped to 2.0
2022-06-17 Development
    o Fixed events.html to allow "" as a valid callsign
2022-06-27 Event update
    o Increased the number of "fox" types are allowed
2022-06-28 Development
    Sleep debug
2022-07-03 Development
    o Corrects a bug that prevented transmit power from being set properly if an antenna was not connected at power-up.
2022-07-03 Development
    o Corrects a bug that could interrupt an event stored in EEPROM if no changes to that event get downloaded from the ESP flash memory
    o Bumped software version to 0.3
2022-07-16 Development
    o Fixes for bugs related to coming out of sleep
    o FET driver is left on, final FET voltage is turned off if no antenna
    o Version 0.4
2023-01-18 Major Update
    o Debug of RTC power up
    o LEDs now indicate hardware failures
    o Green LED now indicates if antenna is attached
2023-01-28 Ver 0.92
    Added on-air transmission following the connection of an antenna.
2023-01-28 Updates
    Schematic
    Fixes to events.html
2023-01-31 Development
    o Added a confirmation transmission that occurs shortly after the antenna is connected, or at power up.
    o Added debounce improvements for the pushbutton and antenna connection detect
2023-02-01 Updates
    o Allow the antenna-connect xmit enunciation to be avoided by plugging the antenna in before power on.
2023-02-02 Ver 0.97
    Tweaks to courtesy antenna-connect transmission.
    Debug of some memory allocation issues for strings
2023-07-07 Ver 0.98
    o Improves synchronization of foxes to under 1 second. Extensive code changes involved to synchronize clock to 1-second transitions.
2023-07-10 Ver 0.99
    Corrects a glitch in the transmit pattern after sending the ID.
2023-07-10 Ver 0.100
    Corrects a small glitch that could occur in the Morse pattern.
2023-07-23 Ver 0.101
    Corrects an error in serial port comms.
2023-10-13 Rev 0.103
    o Brought in changes from NanoFox
    o Fixes bug in multi-event logic that could cause some transmitters to be timed incorrectly
2024-05-06 Bug Fixes
    Fixes a problem with storing the call sign
    Minor bug fixes affecting LED behavior
